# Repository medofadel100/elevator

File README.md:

# elevator
elevator  With Arduino And RFID

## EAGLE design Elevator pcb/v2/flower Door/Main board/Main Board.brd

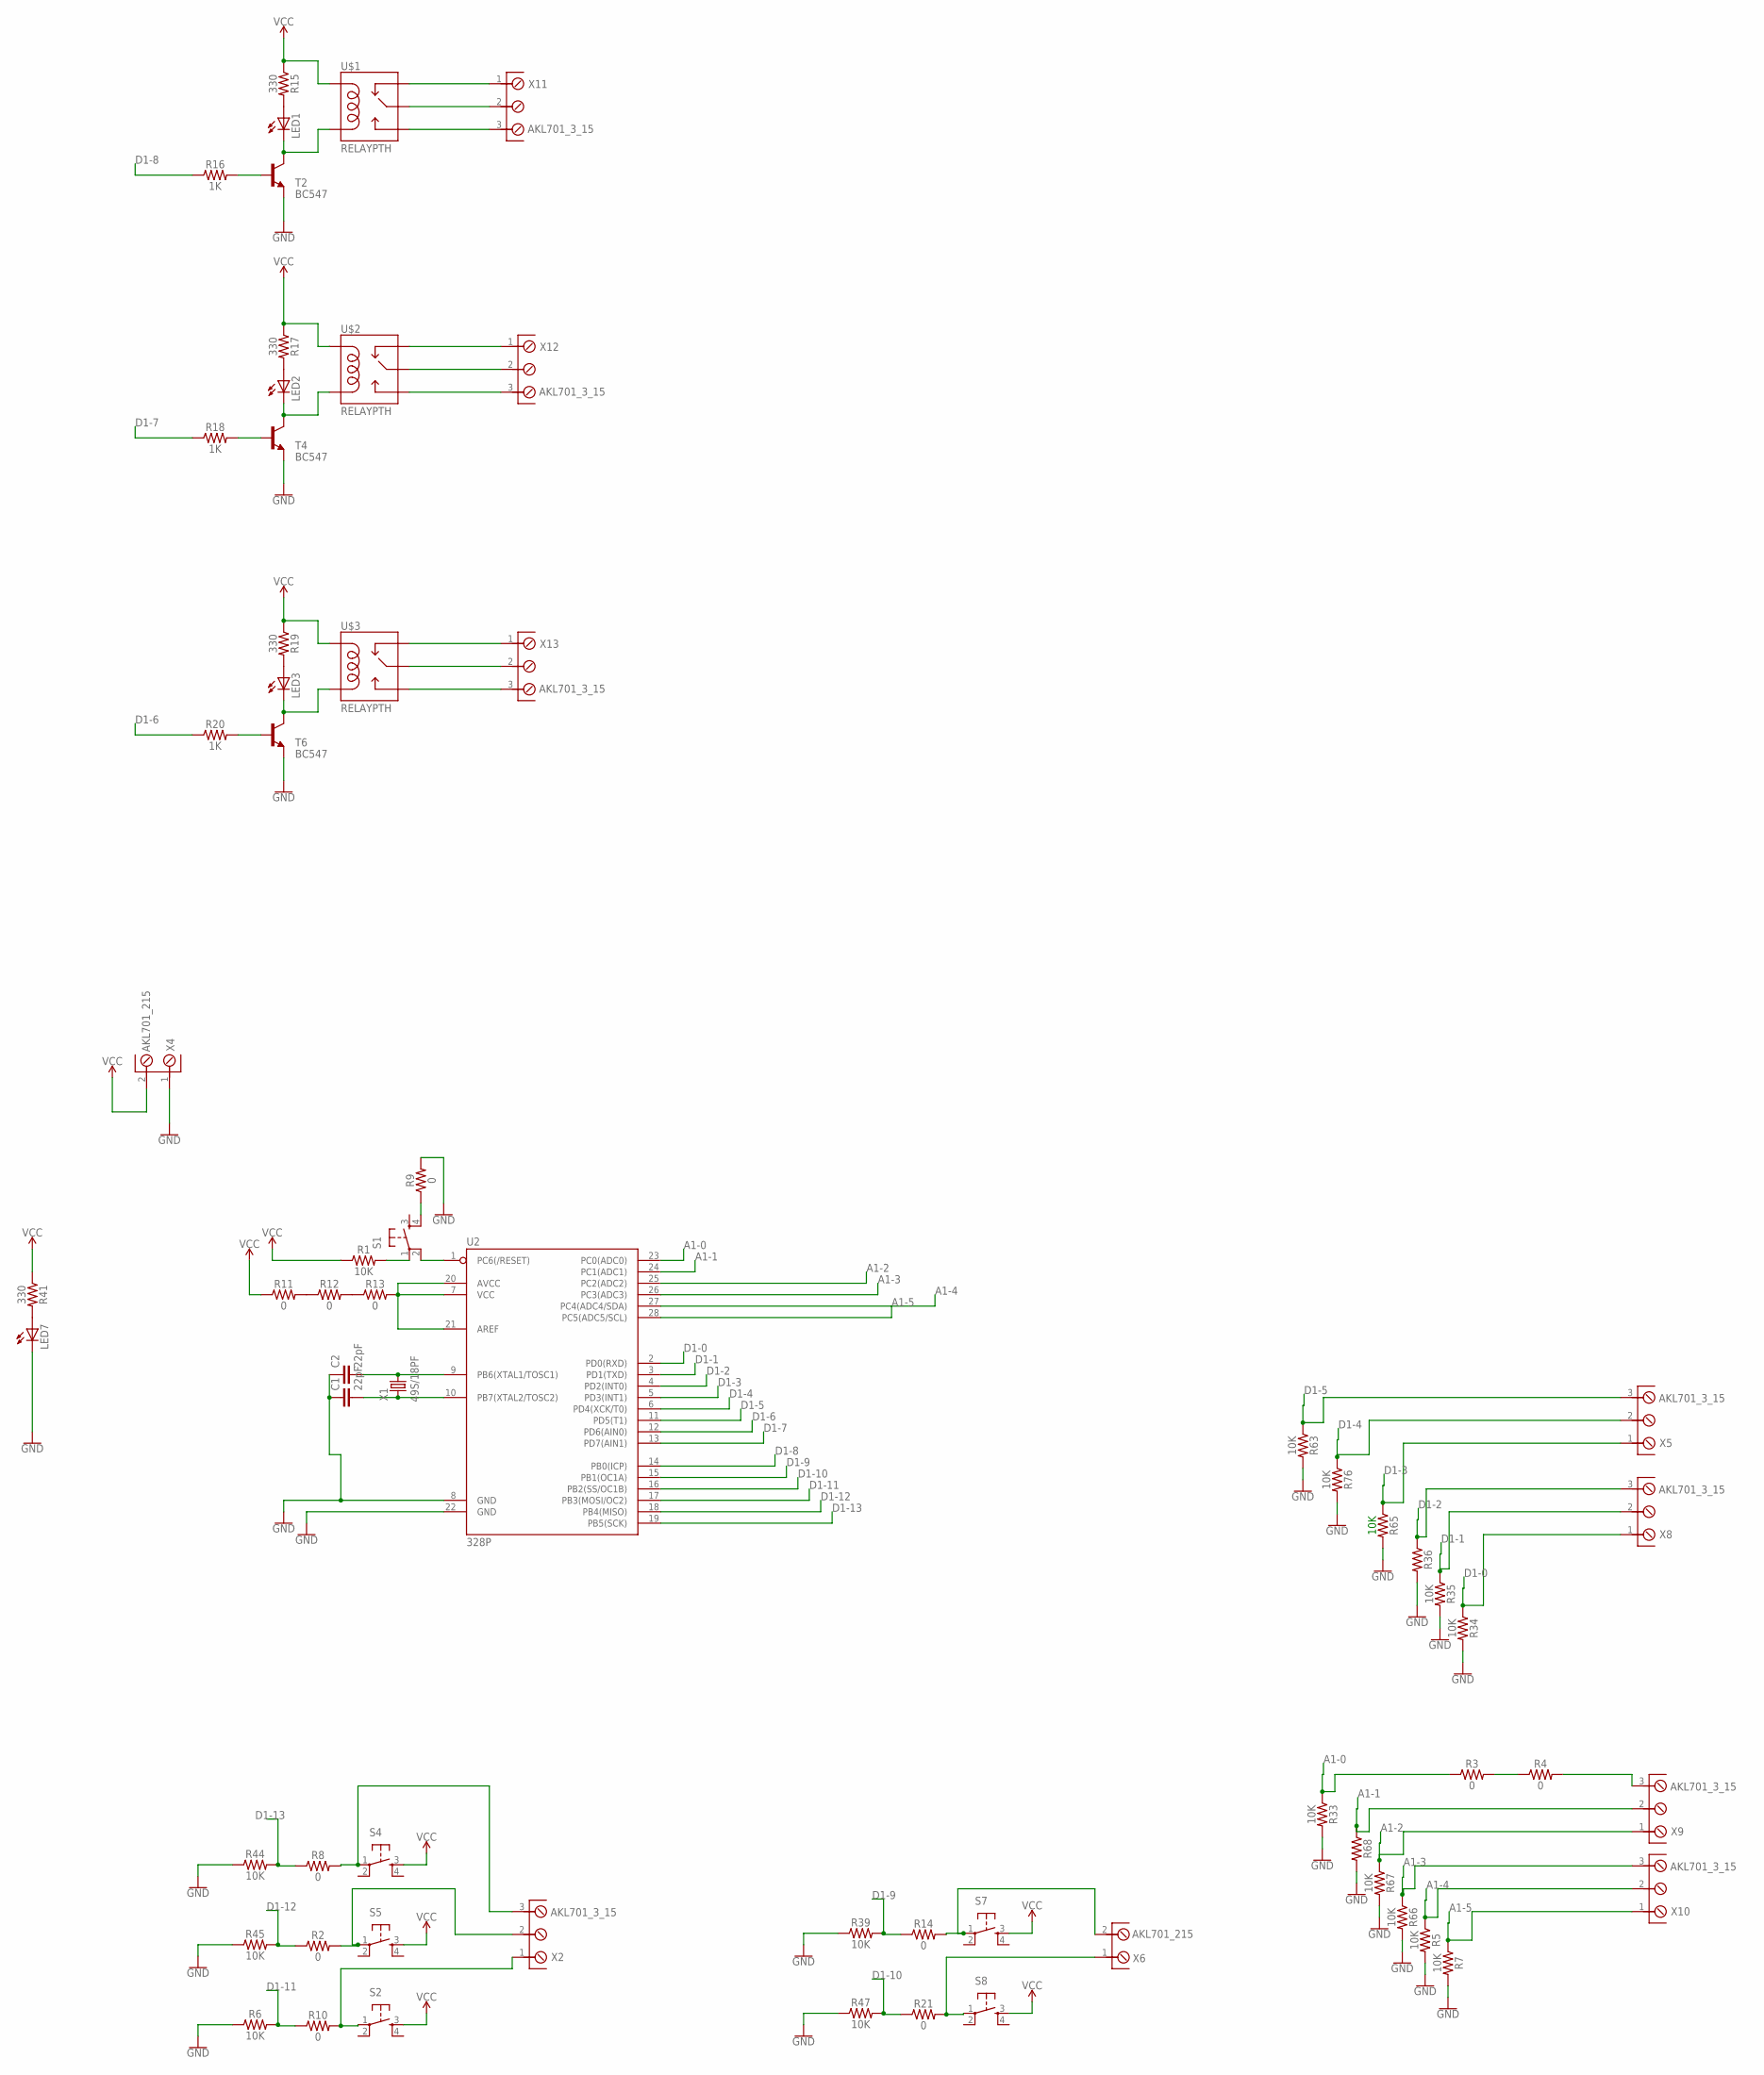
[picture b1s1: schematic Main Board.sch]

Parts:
C1, C2: 22pF; CAP-PTH-2.54
LED1, LED2, LED3, LED7: LED5MM
R1, R5, R6, R7, R33, R34, R35, R36, R39, R44, R45, R47, R63, R65, R66, R67, R68, R76: 10K; AXIAL-0.3
R2, R3, R4, R8, R9, R10, R11, R12, R13, R14, R21: 0; AXIAL-0.3
R15, R17, R19, R41: 330; AXIAL-0.3
R16, R18, R20: 1K; AXIAL-0.3
S1, S2, S4, S5, S7, S8: TAC_SWITCHPTH; TACTILE-PTH
T2, T4, T6: BC547; TO92
U2: 328P; DIP28
U$1, U$2, U$3: RELAYPTH; SRD-05VDC-SL-C
X1: 49S/18PF; XTAL_HC49
X2, X5, X8, X9, X10, X11, X12, X13: AKL701_3_15
X4, X6: AKL701_215; AKL701_2_15

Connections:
A1-0: R3.P$1 (1), R33.P$1 (1), U2.23 (PC0(ADC0))
A1-1: R68.P$1 (1), U2.24 (PC1(ADC1)), X9.2
A1-2: R67.P$1 (1), U2.25 (PC2(ADC2)), X9.1
A1-3: R66.P$1 (1), U2.26 (PC3(ADC3)), X10.3
A1-4: R5.P$1 (1), U2.27 (PC4(ADC4/SDA)), X10.2
A1-5: R7.P$1 (1), U2.28 (PC5(ADC5/SCL)), X10.1
D1-0: R34.P$1 (1), U2.2 (PD0(RXD)), X8.1
D1-1: R35.P$1 (1), U2.3 (PD1(TXD)), X8.2
D1-2: R36.P$1 (1), U2.4 (PD2(INT0)), X8.3
D1-3: R65.P$1 (1), U2.5 (PD3(INT1)), X5.1
D1-4: R76.P$1 (1), U2.6 (PD4(XCK/T0)), X5.2
D1-5: R63.P$1 (1), U2.11 (PD5(T1)), X5.3
D1-6: R20.P$1 (1), U2.12 (PD6(AIN0))
D1-7: R18.P$1 (1), U2.13 (PD7(AIN1))
D1-8: R16.P$1 (1), U2.14 (PB0(ICP))
D1-9: R14.P$1 (1), R39.P$2 (2), U2.15 (PB1(OC1A))
D1-10: R21.P$1 (1), R47.P$2 (2), U2.16 (PB2(SS/OC1B))
D1-11: R6.P$2 (2), R10.P$1 (1), U2.17 (PB3(MOSI/OC2))
D1-12: R2.P$1 (1), R45.P$2 (2), U2.18 (PB4(MISO))
D1-13: R8.P$1 (1), R44.P$2 (2), U2.19 (PB5(SCK))
GND: C1.1, C2.1, LED7.K (C), R5.P$2 (2), R6.P$1 (1), R7.P$2 (2), R9.P$2 (2), R33.P$2 (2), R34.P$2 (2), R35.P$2 (2), R36.P$2 (2), R39.P$1 (1), R44.P$1 (1), R45.P$1 (1), R47.P$1 (1), R63.P$2 (2), R65.P$2 (2), R66.P$2 (2), R67.P$2 (2), R68.P$2 (2), R76.P$2 (2), T2.1 (E), T4.1 (E), T6.1 (E), U2.8 (GND), U2.22 (GND), X4.1
unnamed: C2.2, U2.9 (PB6(XTAL1/TOSC1)), X1.2
unnamed: C1.2, U2.10 (PB7(XTAL2/TOSC2)), X1.1
unnamed: R1.P$2 (2), S1.1
unnamed: S1.2, U2.1 (PC6(/RESET))
unnamed: U$3.SWCLOSED (SWCLOSE), X13.1
unnamed: U$3.SWCOMMON, X13.2
unnamed: U$3.SWOPEN, X13.3
unnamed: U$2.SWCLOSED (SWCLOSE), X12.1
unnamed: LED1.A, R15.P$2 (2)
unnamed: LED1.K (C), T2.3 (C), U$1.COIL0
unnamed: R16.P$2 (2), T2.2 (B)
unnamed: U$2.SWCOMMON, X12.2
unnamed: U$2.SWOPEN, X12.3
unnamed: U$1.SWCLOSED (SWCLOSE), X11.1
unnamed: LED2.A, R17.P$2 (2)
unnamed: LED2.K (C), T4.3 (C), U$2.COIL0
unnamed: R18.P$2 (2), T4.2 (B)
unnamed: U$1.SWCOMMON, X11.2
unnamed: U$1.SWOPEN, X11.3
unnamed: R10.P$2 (2), S2.1, X2.1
unnamed: LED3.A, R19.P$2 (2)
unnamed: LED3.K (C), T6.3 (C), U$3.COIL0
unnamed: R20.P$2 (2), T6.2 (B)
unnamed: R2.P$2 (2), S5.1, X2.2
unnamed: R4.P$2 (2), X9.3
unnamed: R3.P$2 (2), R4.P$1 (1)
unnamed: R8.P$2 (2), S4.1, X2.3
unnamed: R14.P$2 (2), S7.1, X6.2
unnamed: R21.P$2 (2), S8.1, X6.1
unnamed: LED7.A, R41.P$2 (2)
unnamed: R9.P$1 (1), S1.4
unnamed: R13.P$2 (2), U2.7 (VCC), U2.20 (AVCC), U2.21 (AREF)
unnamed: R11.P$2 (2), R12.P$1 (1)
unnamed: R12.P$2 (2), R13.P$1 (1)
VCC: R1.P$1 (1), R11.P$1 (1), R15.P$1 (1), R17.P$1 (1), R19.P$1 (1), R41.P$1 (1), S2.3, S4.3, S5.3, S7.3, S8.3, U$1.COIL1, U$2.COIL1, U$3.COIL1, X4.2

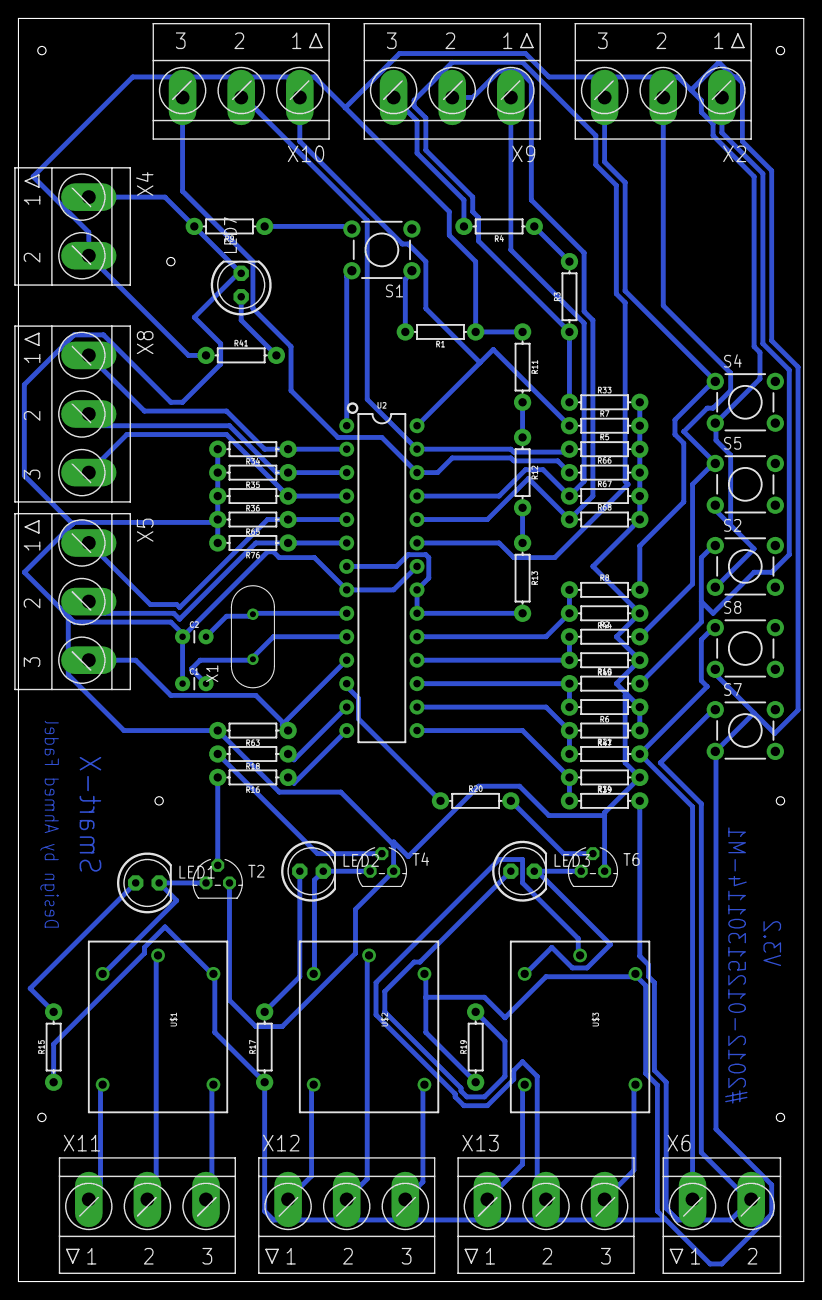
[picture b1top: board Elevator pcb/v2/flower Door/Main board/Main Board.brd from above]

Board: 1 copper layer, 85.1 x 136.8 mm, 66 parts (0 on the bottom side), 56 nets.

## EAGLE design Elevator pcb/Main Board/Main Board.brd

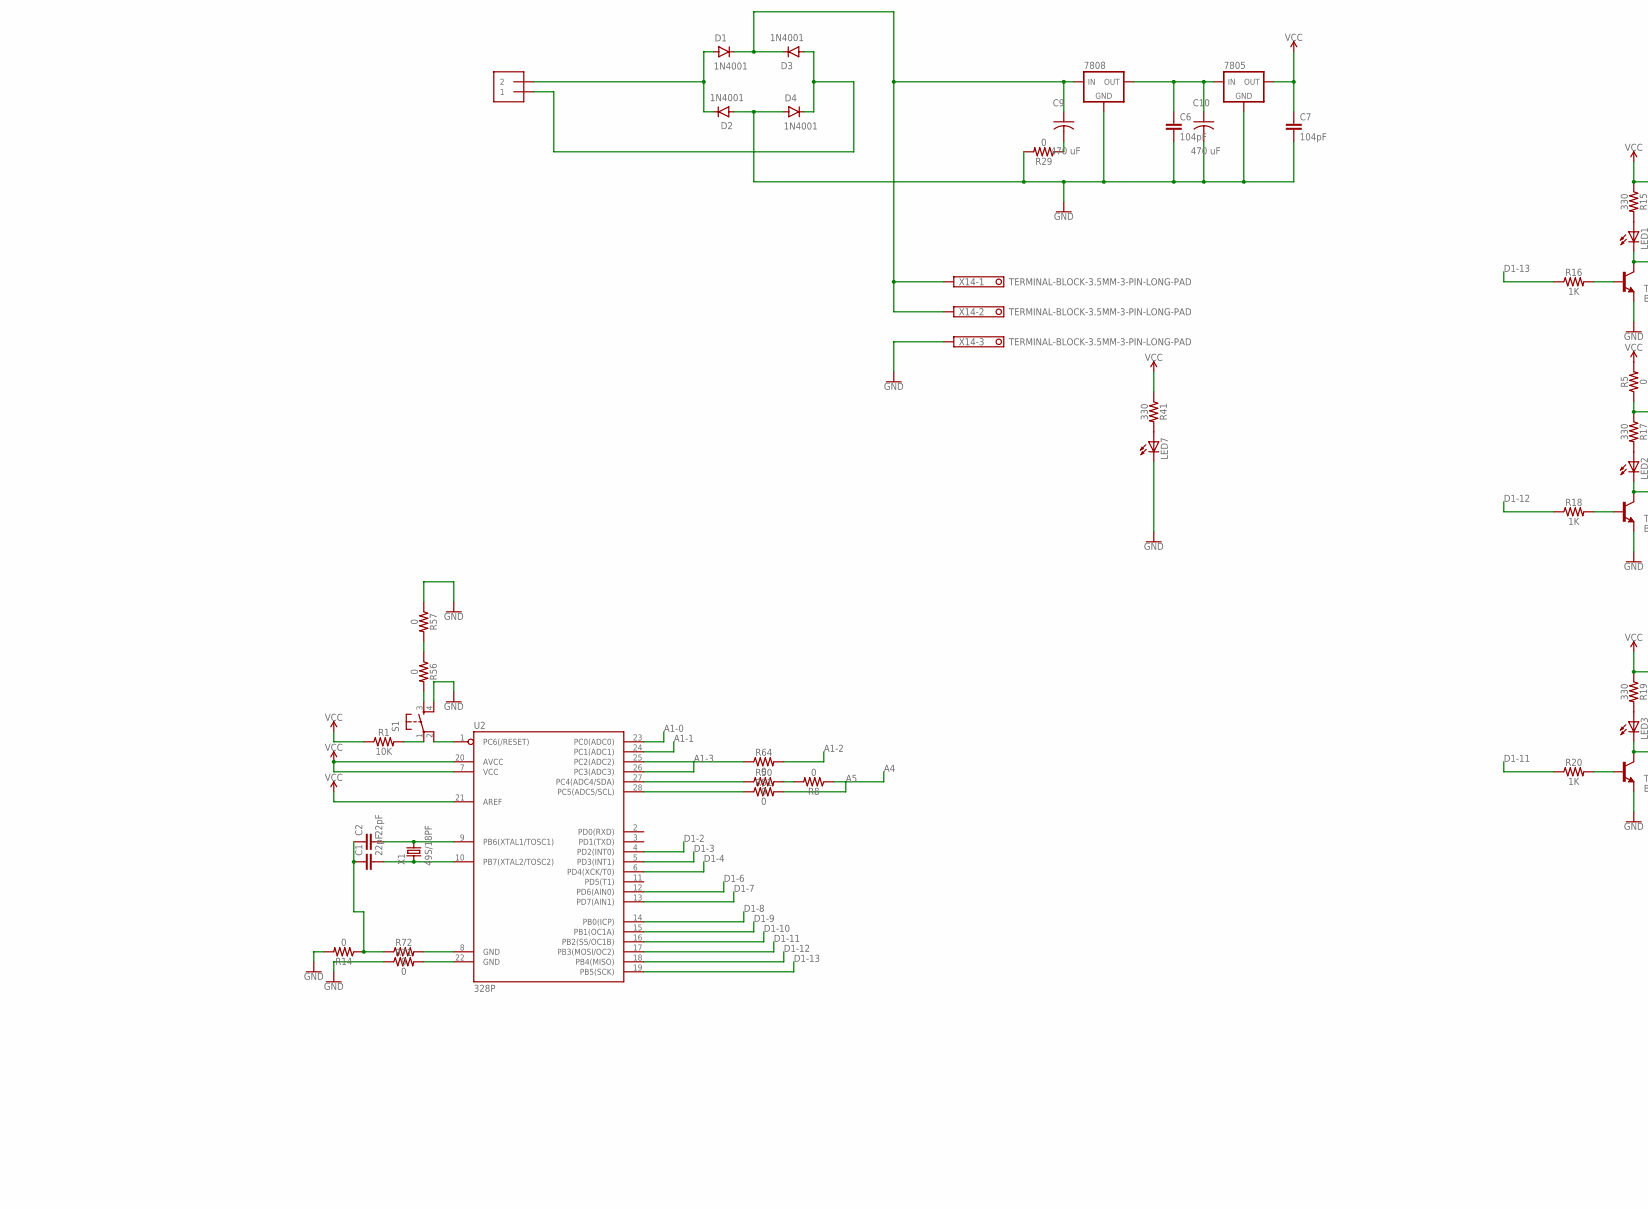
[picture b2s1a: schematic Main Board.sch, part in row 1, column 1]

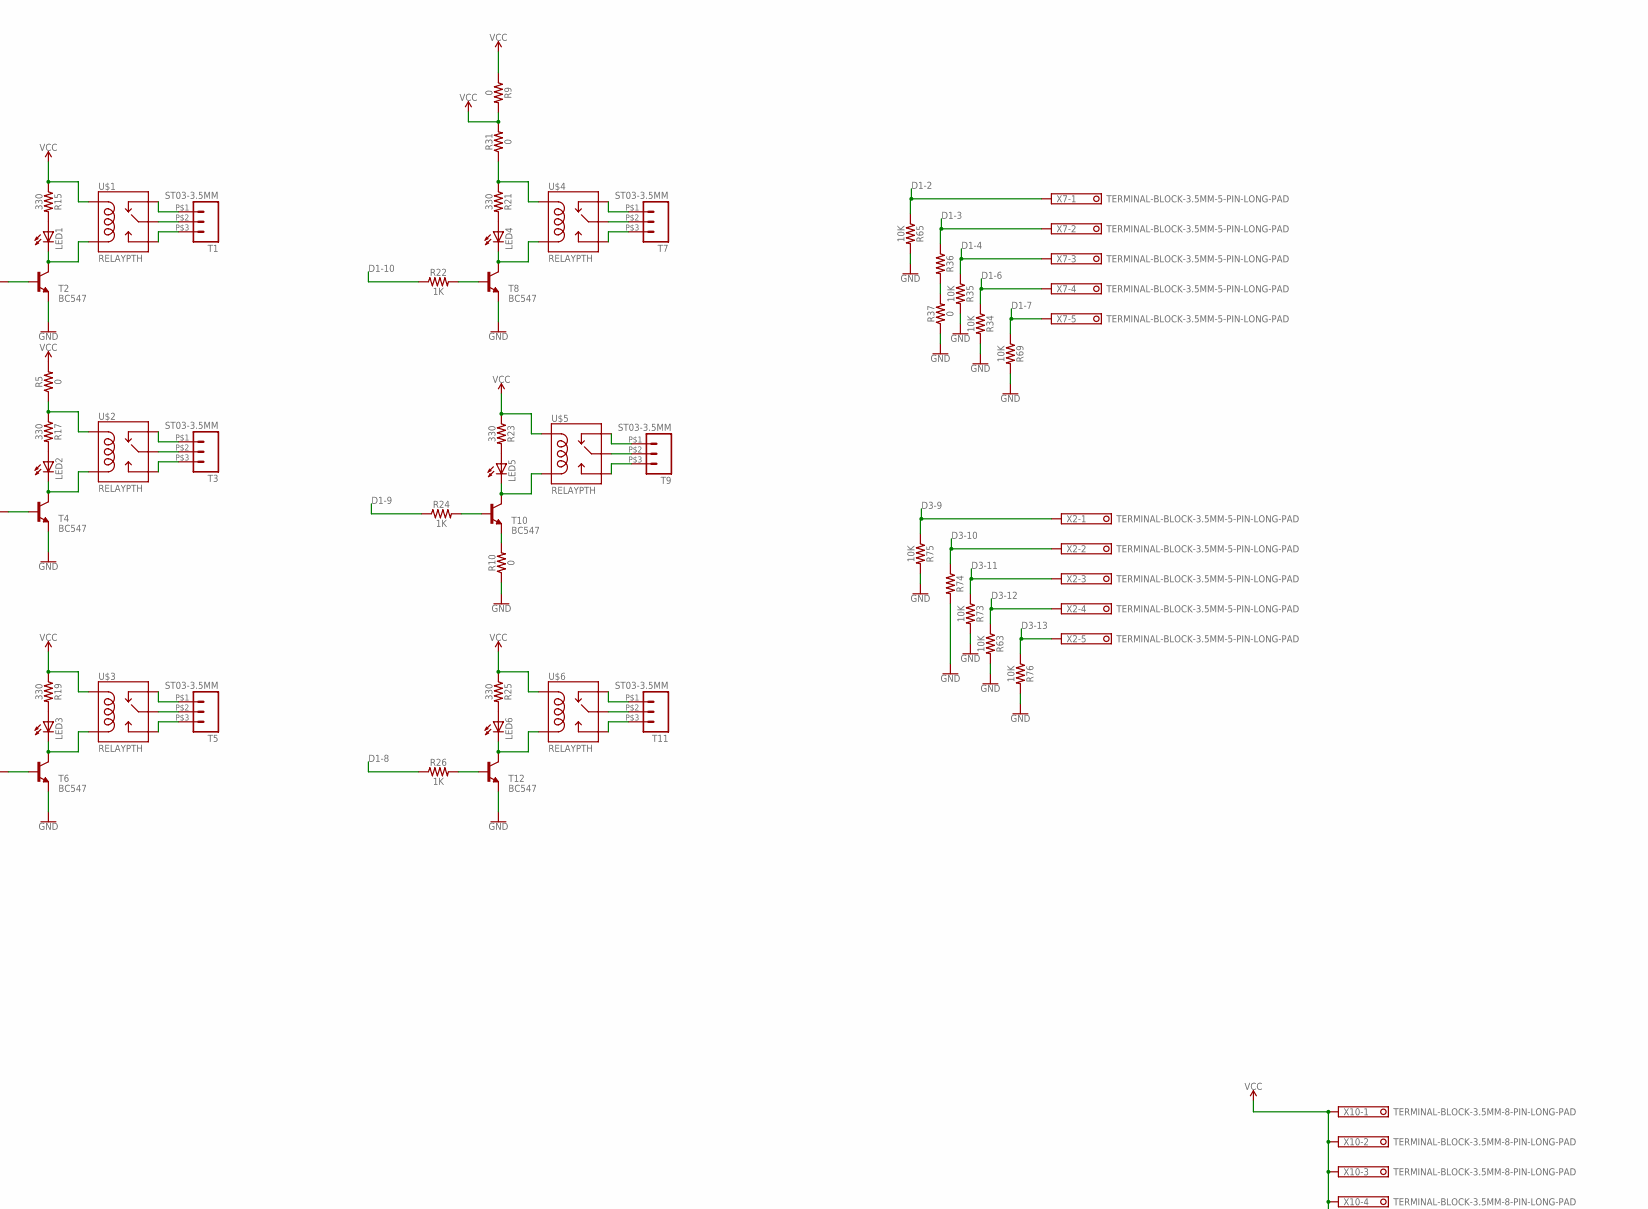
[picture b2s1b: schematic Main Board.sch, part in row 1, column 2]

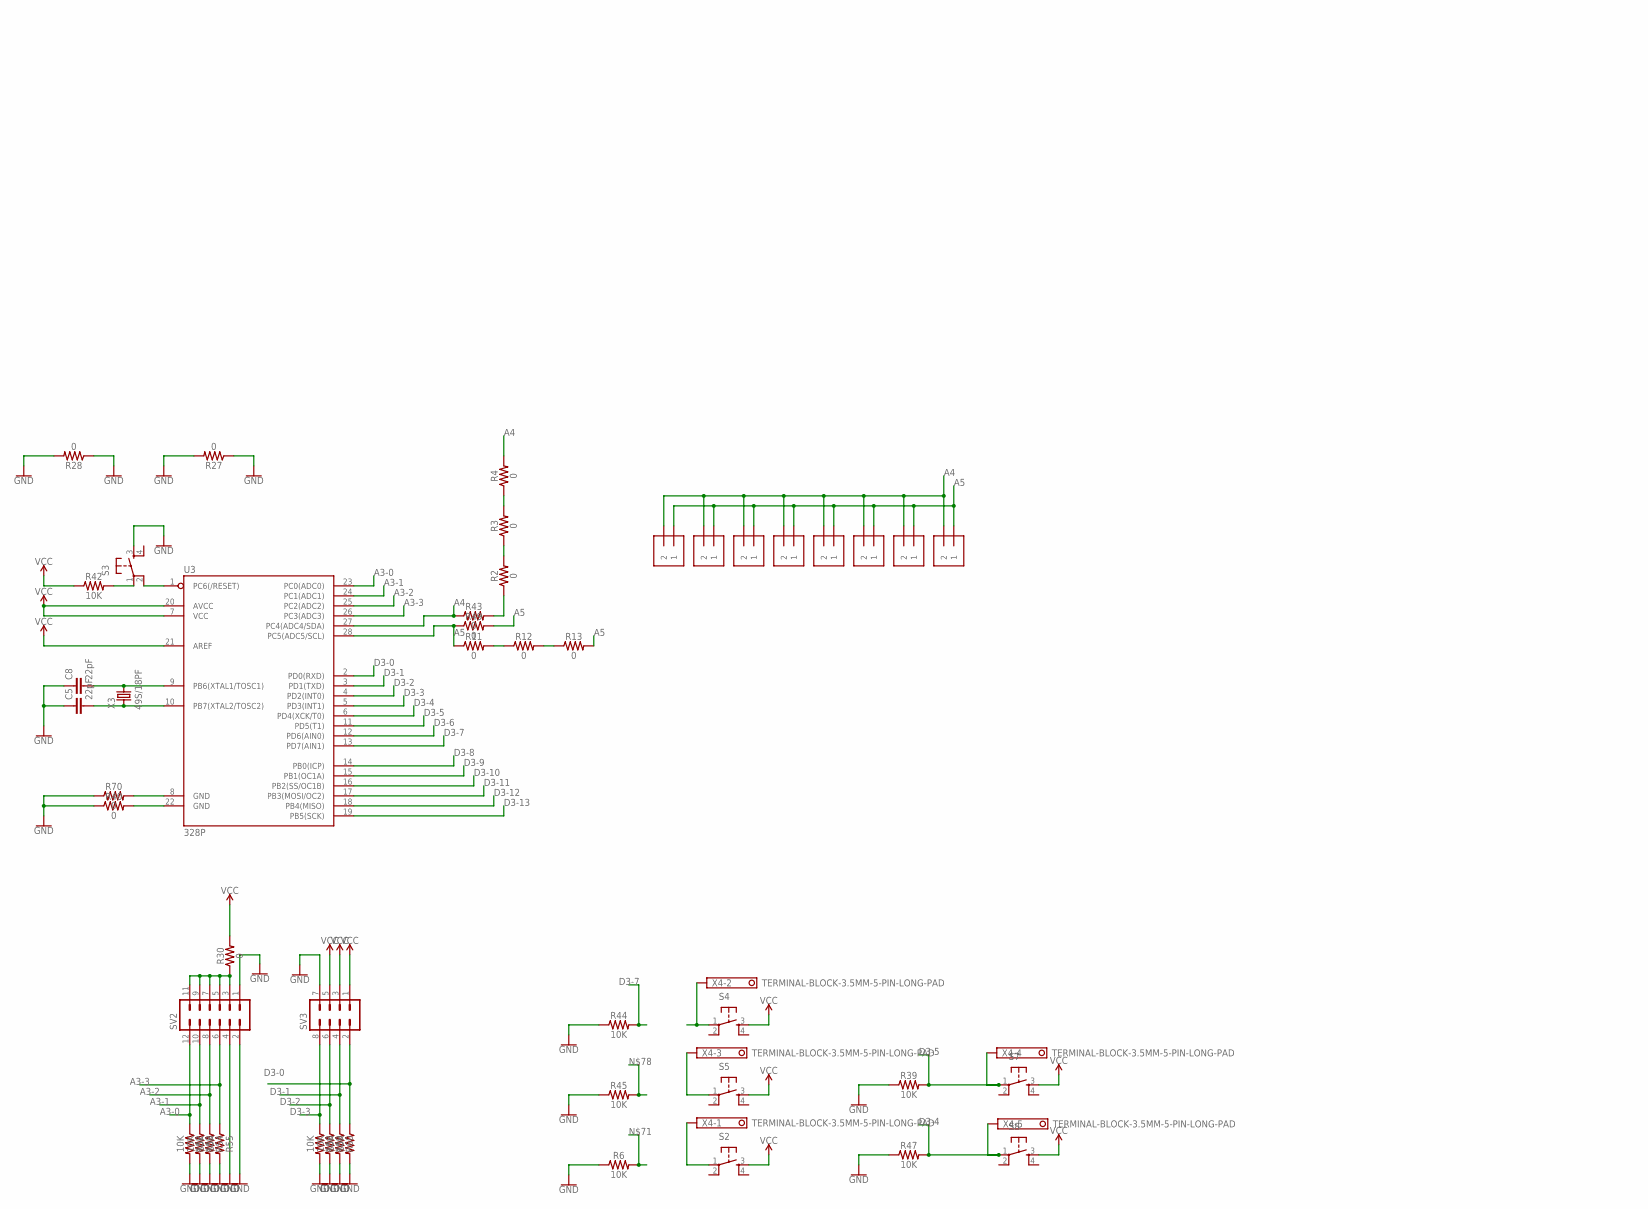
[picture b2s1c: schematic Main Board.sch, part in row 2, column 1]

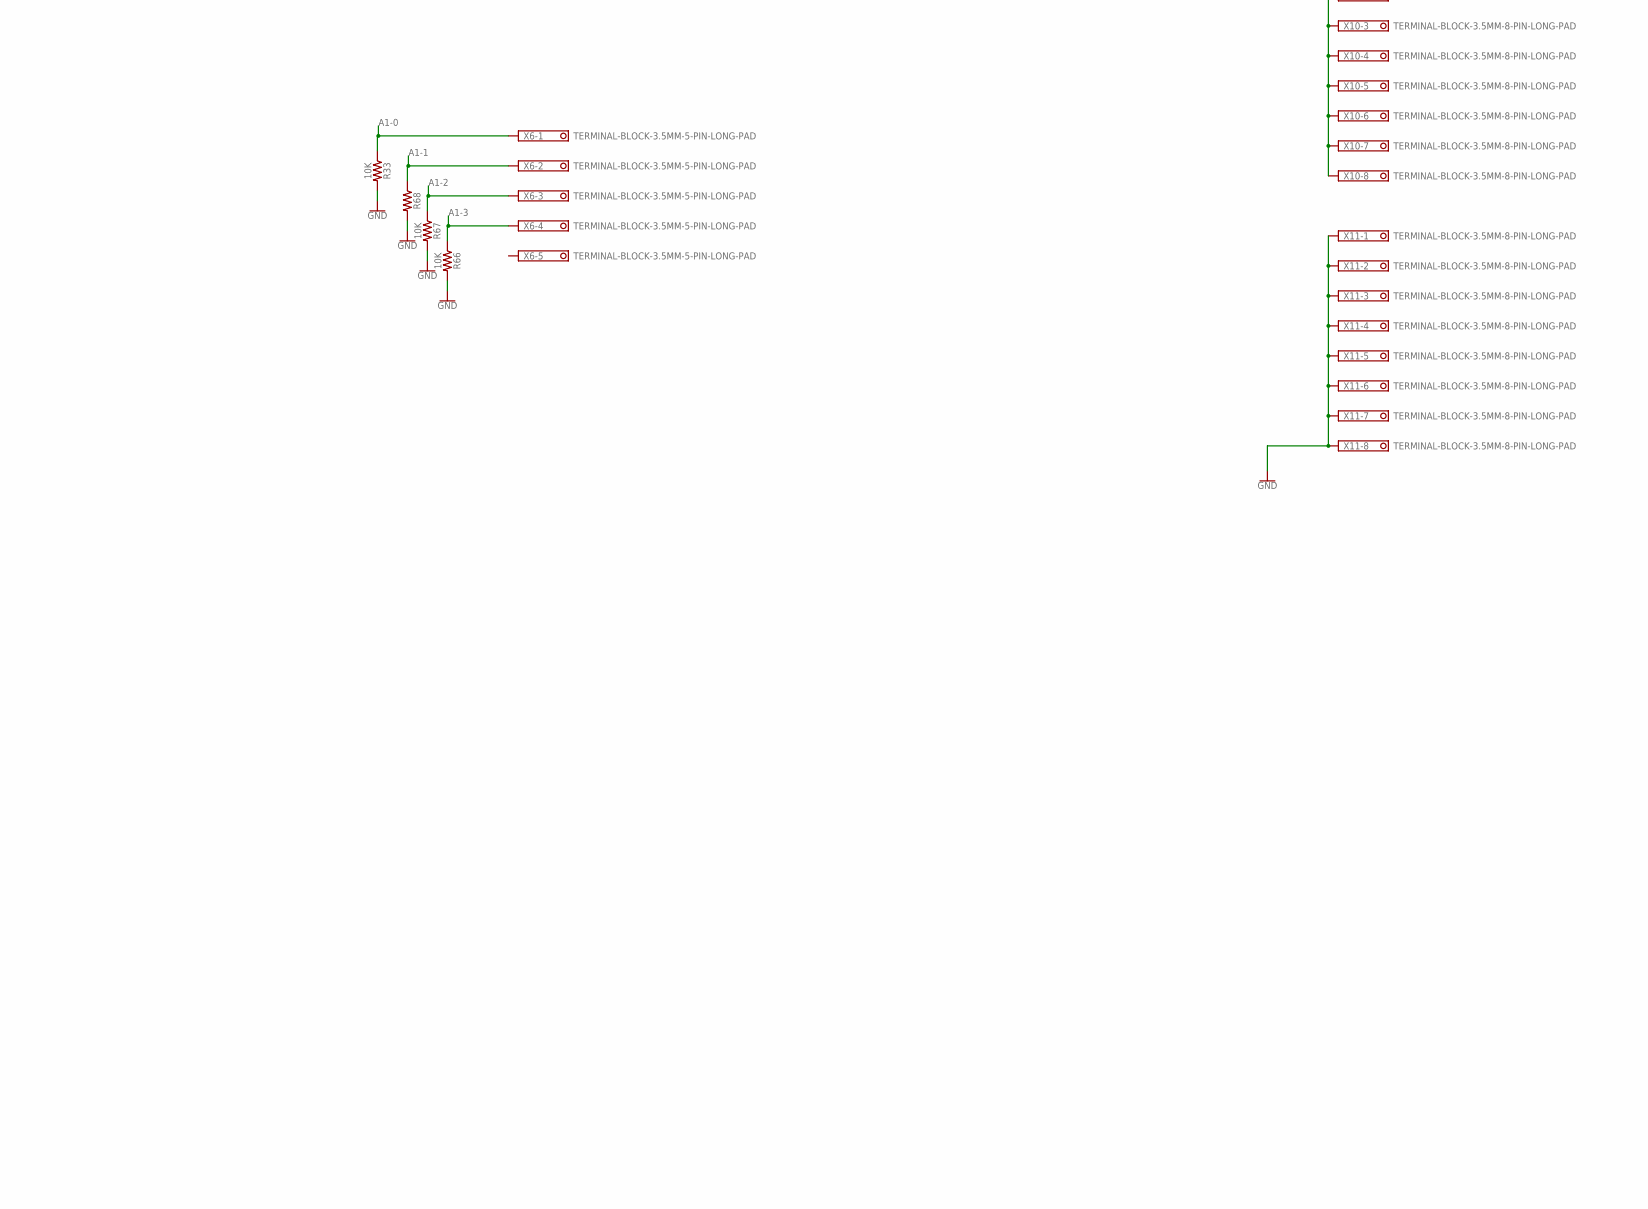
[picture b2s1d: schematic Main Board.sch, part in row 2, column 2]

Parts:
7805, 7808: 78XX-TO220H-NH; TO220BH-NH
C1, C2, C5, C8: 22pF; CAP-PTH-2.54
C6, C7: 104pF; CAP-PTH-2.54
C9, C10: 470 uF; CAP_RADIAL_5MM
D1, D2, D3, D4: 1N4001; DO-41
LED1, LED2, LED3, LED4, LED5, LED6, LED7: LED5MM
POWER-INPUT, POWER-INPUT1, POWER-INPUT2, POWER-INPUT3, POWER-INPUT4, POWER-INPUT5, POWER-INPUT6, POWER-INPUT7, POWER-INPUT8: 1X2-3.5MM
R1, R6, R33, R34, R35, R36, R39, R42, R44, R45, R47, R52, R53, R54, R55, R58, R59, R60, R61, R63, R65, R66, R67, R68, R69, R73, R74, R75, R76: 10K; AXIAL-0.3
R2, R3, R4, R5, R8, R9, R10, R11, R12, R13, R14, R27, R28, R29, R30, R31, R37, R40, R43, R49, R50, R51, R56, R57, R64, R70, R71, R72: 0; AXIAL-0.3
R15, R17, R19, R21, R23, R25, R41: 330; AXIAL-0.3
R16, R18, R20, R22, R24, R26: 1K; AXIAL-0.3
S1, S2, S3, S4, S5, S7, S8: TAC_SWITCHPTH; TACTILE-PTH
SV2: MA06-2
SV3: MA04-2
T1, T3, T5, T7, T9, T11: ST03-3.5MM; ED350V-03P
T2, T4, T6, T8, T10, T12: BC547; TO92
U2, U3: 328P; DIP28
U$1, U$2, U$3, U$4, U$5, U$6: RELAYPTH; SRD-05VDC-SL-C
X1, X3: 49S/18PF; XTAL_HC49
X2, X4, X6, X7: TERMINAL-BLOCK-3.5MM-5-PIN-LONG-PAD; TERMINAL-BLOCK-5-PIN-3.5MM-LONG-PAD
X10, X11: TERMINAL-BLOCK-3.5MM-8-PIN-LONG-PAD; TERMINAL-BLOCK-8-PIN-3.5MM-LONG-PAD
X14: TERMINAL-BLOCK-3.5MM-3-PIN-LONG-PAD; TERMINAL-BLOCK-3-PIN-3.5MM-LONG-PAD

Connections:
A1-0: R33.P$1 (1), U2.23 (PC0(ADC0)), X6.1
A1-1: R68.P$1 (1), U2.24 (PC1(ADC1)), X6.2
A1-2: R64.P$2 (2), R67.P$1 (1), X6.3
A1-3: R66.P$1 (1), U2.26 (PC3(ADC3)), X6.4
A3-0: R52.P$1 (1), SV2.12, U3.23 (PC0(ADC0))
A3-1: R53.P$1 (1), SV2.10, U3.24 (PC1(ADC1))
A3-2: R54.P$1 (1), SV2.8, U3.25 (PC2(ADC2))
A3-3: R55.P$1 (1), SV2.6, U3.26 (PC3(ADC3))
A4: POWER-INPUT1.2, POWER-INPUT2.2, POWER-INPUT3.2, POWER-INPUT4.2, POWER-INPUT5.2, POWER-INPUT6.2, POWER-INPUT7.2, POWER-INPUT8.2, R4.P$2 (2), R8.P$1 (1), R43.P$1 (1), U3.27 (PC4(ADC4/SDA))
A5: POWER-INPUT1.1, POWER-INPUT2.1, POWER-INPUT3.1, POWER-INPUT4.1, POWER-INPUT5.1, POWER-INPUT6.1, POWER-INPUT7.1, POWER-INPUT8.1, R11.P$1 (1), R13.P$2 (2), R49.P$1 (1), R49.P$2 (2), R51.P$2 (2), U3.28 (PC5(ADC5/SCL))
D1-2: R65.P$1 (1), U2.4 (PD2(INT0)), X7.1
D1-3: R36.P$1 (1), U2.5 (PD3(INT1)), X7.2
D1-4: R35.P$1 (1), U2.6 (PD4(XCK/T0)), X7.3
D1-6: R34.P$1 (1), U2.12 (PD6(AIN0)), X7.4
D1-7: R69.P$1 (1), U2.13 (PD7(AIN1)), X7.5
D1-8: R26.P$1 (1), U2.14 (PB0(ICP))
D1-9: R24.P$1 (1), U2.15 (PB1(OC1A))
D1-10: R22.P$1 (1), U2.16 (PB2(SS/OC1B))
D1-11: R20.P$1 (1), U2.17 (PB3(MOSI/OC2))
D1-12: R18.P$1 (1), U2.18 (PB4(MISO))
D1-13: R16.P$1 (1), U2.19 (PB5(SCK))
D3-0: R61.P$1 (1), SV3.2, U3.2 (PD0(RXD))
D3-1: R60.P$1 (1), SV3.4, U3.3 (PD1(TXD))
D3-2: R59.P$1 (1), SV3.6, U3.4 (PD2(INT0))
D3-3: R58.P$1 (1), SV3.8, U3.5 (PD3(INT1))
D3-4: R47.P$2 (2), S8.1, U3.6 (PD4(XCK/T0)), X4.5
D3-5: R39.P$2 (2), S7.1, U3.11 (PD5(T1)), X4.4
D3-10: R74.P$1 (1), U3.16 (PB2(SS/OC1B)), X2.2
D3-11: R73.P$1 (1), U3.17 (PB3(MOSI/OC2)), X2.3
D3-12: R63.P$1 (1), U3.18 (PB4(MISO)), X2.4
D3-13: R76.P$1 (1), U3.19 (PB5(SCK)), X2.5
GND: 7805.2 (GND), 7808.2 (GND), C5.1, C6.2, C7.2, C8.1, C10.2, D2.A, D4.A, LED7.K (C), R6.P$1 (1), R10.P$1 (1), R14.P$2 (2), R27.P$1 (1), R27.P$2 (2), R28.P$1 (1), R28.P$2 (2), R29.P$2 (2), R33.P$2 (2), R34.P$2 (2), R35.P$2 (2), R37.P$1 (1), R39.P$1 (1), R40.P$1 (1), R44.P$1 (1), R45.P$1 (1), R47.P$1 (1), R52.P$2 (2), R53.P$2 (2), R54.P$2 (2), R55.P$2 (2), R57.P$1 (1), R58.P$2 (2), R59.P$2 (2), R60.P$2 (2), R61.P$2 (2), R63.P$2 (2), R65.P$2 (2), R66.P$2 (2), R67.P$2 (2), R68.P$2 (2), R69.P$2 (2), R70.P$1 (1), R71.P$1 (1), R73.P$2 (2), R74.P$2 (2), R75.P$2 (2), R76.P$2 (2), S1.4, S3.3, SV2.1, SV2.2, SV2.4, SV3.7, T2.1 (E), T4.1 (E), T6.1 (E), T8.1 (E), T12.1 (E), X11.1, X11.2, X11.3, X11.4, X11.5, X11.6, X11.7, X11.8, X14.3
unnamed: C2.2, U2.9 (PB6(XTAL1/TOSC1)), X1.2
unnamed: C1.2, U2.10 (PB7(XTAL2/TOSC2)), X1.1
unnamed: R1.P$2 (2), S1.1
unnamed: S1.2, U2.1 (PC6(/RESET))
unnamed: R2.P$1 (1), R43.P$2 (2)
unnamed: R2.P$2 (2), R3.P$1 (1)
unnamed: R3.P$2 (2), R4.P$1 (1)
unnamed: R5.P$1 (1), R17.P$1 (1), U$2.COIL1
unnamed: LED1.A, R15.P$2 (2)
unnamed: LED1.K (C), T2.3 (C), U$1.COIL0
unnamed: R16.P$2 (2), T2.2 (B)
unnamed: T1.P$2 (2), U$1.SWCOMMON
unnamed: T1.P$1 (1), U$1.SWCLOSED (SWCLOSE)
unnamed: T1.P$3 (3), U$1.SWOPEN
unnamed: LED2.A, R17.P$2 (2)
unnamed: LED2.K (C), T4.3 (C), U$2.COIL0
unnamed: R18.P$2 (2), T4.2 (B)
unnamed: T3.P$2 (2), U$2.SWCOMMON
unnamed: T3.P$1 (1), U$2.SWCLOSED (SWCLOSE)
unnamed: T3.P$3 (3), U$2.SWOPEN
unnamed: LED3.A, R19.P$2 (2)
unnamed: LED3.K (C), T6.3 (C), U$3.COIL0
unnamed: R20.P$2 (2), T6.2 (B)
unnamed: T5.P$2 (2), U$3.SWCOMMON
unnamed: T5.P$1 (1), U$3.SWCLOSED (SWCLOSE)
unnamed: T5.P$3 (3), U$3.SWOPEN
unnamed: LED4.A, R21.P$2 (2)
unnamed: LED4.K (C), T8.3 (C), U$4.COIL0
unnamed: R22.P$2 (2), T8.2 (B)
unnamed: T7.P$2 (2), U$4.SWCOMMON
unnamed: T7.P$1 (1), U$4.SWCLOSED (SWCLOSE)
unnamed: T7.P$3 (3), U$4.SWOPEN
unnamed: LED5.A, R23.P$2 (2)
unnamed: LED5.K (C), T10.3 (C), U$5.COIL0
unnamed: R24.P$2 (2), T10.2 (B)
unnamed: T9.P$2 (2), U$5.SWCOMMON
unnamed: T9.P$1 (1), U$5.SWCLOSED (SWCLOSE)
unnamed: T9.P$3 (3), U$5.SWOPEN
unnamed: LED6.A, R25.P$2 (2)
unnamed: LED6.K (C), T12.3 (C), U$6.COIL0
unnamed: R26.P$2 (2), T12.2 (B)
unnamed: T11.P$2 (2), U$6.SWCOMMON
unnamed: T11.P$1 (1), U$6.SWCLOSED (SWCLOSE)
unnamed: T11.P$3 (3), U$6.SWOPEN
unnamed: 7808.1 (VIN), C9.1, D1.C, D3.C, X14.1, X14.2
unnamed: LED7.A, R41.P$2 (2)
unnamed: D3.A, D4.C, POWER-INPUT.1
unnamed: D1.A, D2.C, POWER-INPUT.2
unnamed: C8.2, U3.9 (PB6(XTAL1/TOSC1)), X3.2
unnamed: 7805.1 (VIN), 7808.3 (VOUT), C6.1, C10.1
unnamed: C5.2, U3.10 (PB7(XTAL2/TOSC2)), X3.1
unnamed: R42.P$2 (2), S3.1
unnamed: S3.2, U3.1 (PC6(/RESET))
unnamed: C9.2, R29.P$1 (1)
unnamed: C1.1, C2.1, R14.P$1 (1), R72.P$1 (1)
unnamed: R11.P$2 (2), R12.P$1 (1)
unnamed: R50.P$1 (1), U2.27 (PC4(ADC4/SDA))
unnamed: R51.P$1 (1), U2.28 (PC5(ADC5/SCL))
unnamed: R64.P$1 (1), U2.25 (PC2(ADC2))
unnamed: R10.P$2 (2), T10.1 (E)
unnamed: R12.P$2 (2), R13.P$1 (1)
unnamed: R40.P$2 (2), U3.22 (GND)
unnamed: R70.P$2 (2), U3.8 (GND)
unnamed: R71.P$2 (2), U2.22 (GND)
unnamed: R72.P$2 (2), U2.8 (GND)
unnamed: R8.P$2 (2), R50.P$2 (2)
unnamed: R30.P$1 (1), SV2.3, SV2.5, SV2.7, SV2.9, SV2.11
unnamed: R21.P$1 (1), R31.P$1 (1), U$4.COIL1
unnamed: R36.P$2 (2), R37.P$2 (2)
unnamed: R56.P$2 (2), S1.3
unnamed: R56.P$1 (1), R57.P$2 (2)
VCC: 7805.3 (VOUT), C7.1, R1.P$1 (1), R5.P$2 (2), R9.P$1 (1), R9.P$2 (2), R15.P$1 (1), R19.P$1 (1), R23.P$1 (1), R25.P$1 (1), R30.P$2 (2), R31.P$2 (2), R41.P$1 (1), R42.P$1 (1), S2.3, S4.3, S5.3, S7.3, S8.3, SV3.1, SV3.3, SV3.5, U2.7 (VCC), U2.20 (AVCC), U2.21 (AREF), U3.7 (VCC), U3.20 (AVCC), U3.21 (AREF), U$1.COIL1, U$3.COIL1, U$5.COIL1, U$6.COIL1, X10.1, X10.2, X10.3, X10.4, X10.5, X10.6, X10.7, X10.8

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
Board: 1 copper layer, 138 parts (5 on the bottom side), 108 nets, no tracks yet.

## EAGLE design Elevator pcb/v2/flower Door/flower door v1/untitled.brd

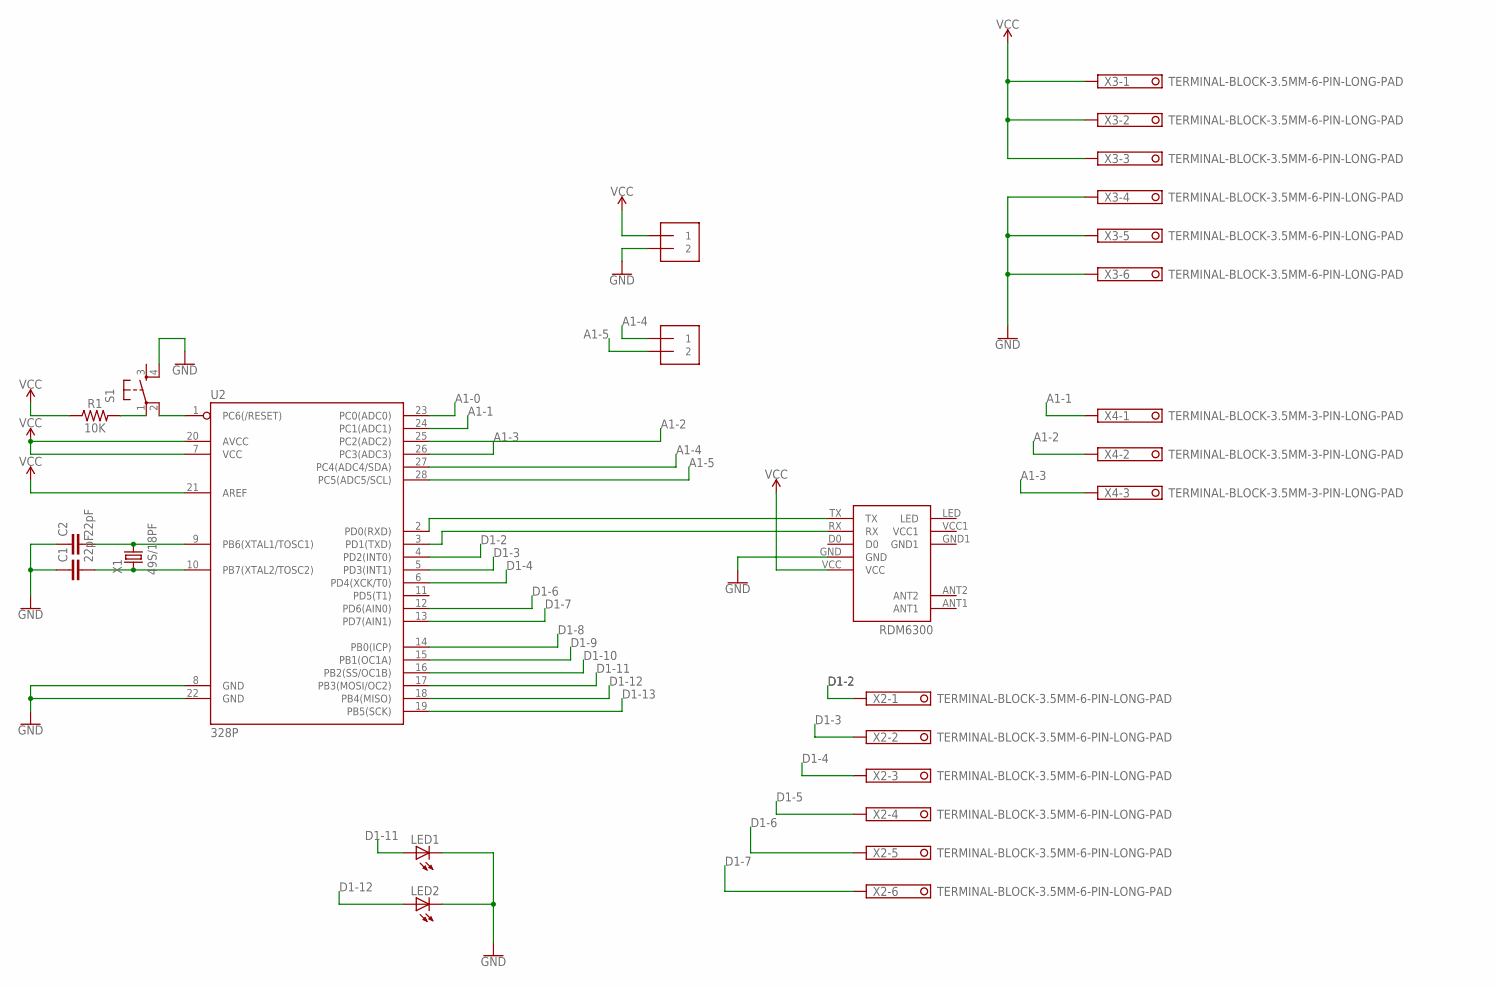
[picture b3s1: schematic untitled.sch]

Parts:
C1, C2: 22pF; CAP-PTH-2.54
J1, J2: 1X2-3.5MM
LED1, LED2: LED5MM
R1: 10K; AXIAL-0.3
RDM1: RDM6300
S1: TAC_SWITCHPTH; TACTILE-PTH
U2: 328P; DIP28
X1: 49S/18PF; XTAL_HC49
X2, X3: TERMINAL-BLOCK-3.5MM-6-PIN-LONG-PAD; TERMINAL-BLOCK-6-PIN-3.5MM-LONG-PAD
X4: TERMINAL-BLOCK-3.5MM-3-PIN-LONG-PAD; TERMINAL-BLOCK-3-PIN-3.5MM-LONG-PAD

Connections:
A1-0: U2.23 (PC0(ADC0))
A1-1: U2.24 (PC1(ADC1)), X4.1
A1-2: U2.25 (PC2(ADC2)), X4.2
A1-3: U2.26 (PC3(ADC3)), X4.3
A1-4: J2.1, U2.27 (PC4(ADC4/SDA))
A1-5: J2.2, U2.28 (PC5(ADC5/SCL))
D1-2: U2.4 (PD2(INT0)), X2.1
D1-3: U2.5 (PD3(INT1)), X2.2
D1-4: U2.6 (PD4(XCK/T0)), X2.3
D1-5: X2.4
D1-6: U2.12 (PD6(AIN0)), X2.5
D1-7: U2.13 (PD7(AIN1)), X2.6
D1-8: U2.14 (PB0(ICP))
D1-9: U2.15 (PB1(OC1A))
D1-10: U2.16 (PB2(SS/OC1B))
D1-11: LED1.A, U2.17 (PB3(MOSI/OC2))
D1-12: LED2.A, U2.18 (PB4(MISO))
D1-13: U2.19 (PB5(SCK))
GND: C1.1, C2.1, J1.2, LED1.K (C), LED2.K (C), RDM1.GND, S1.4, U2.8 (GND), U2.22 (GND), X3.4, X3.5, X3.6
unnamed: C2.2, U2.9 (PB6(XTAL1/TOSC1)), X1.2
unnamed: C1.2, U2.10 (PB7(XTAL2/TOSC2)), X1.1
unnamed: R1.P$2 (2), S1.1
unnamed: S1.2, U2.1 (PC6(/RESET))
unnamed: RDM1.TX, U2.2 (PD0(RXD))
unnamed: RDM1.RX, U2.3 (PD1(TXD))
VCC: J1.1, R1.P$1 (1), RDM1.VCC, U2.7 (VCC), U2.20 (AVCC), U2.21 (AREF), X3.1, X3.2, X3.3

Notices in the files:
parts and their libraries:
SparkFun-Capacitors: Licensing: Creative Commons ShareAlike 4.0 International - https://creativecommons.org/licenses/by-sa/4.0
